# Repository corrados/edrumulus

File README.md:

# Edrumulus

**Edrumulus** is a high quality Open Source e-drum trigger module software which runs on a micro processor.

Project requirements:
- The trigger performance shall be similar to the Roland TD-27.
- Overall latency should be as small as possible. The goal is to achieve a latency < 10 ms.
- The required analog front end design shall be as simple as possible using the fewest number of
  parts possible.

## Videos

## News

Find all important updates of the Edrumulus project in the [change log file](doc/ChangeLog.md)
and in the [discussion forums](https://github.com/corrados/edrumulus/discussions). A road map
of the Edrumulus project can be found in the [TODO file](doc/TODO.md).

## Features

- Positional sensing
- Retrigger cancellation
- Rim shot/cymbol choke detection
- Cross talk cancellation
- Clipping compensation
- Supported micro processor developer boards:
  - **ESP32 (dual core) DEVKIT V1 or similar**
  - **ESP32-S3**
  - **Teensy 4.0/4.1**

## Documentation

- [Manual](doc/manual.md)
- [Algorithm](doc/algorithm.md)

## Prototype hardware

We want to capture the entire signal without non-linear analog preprocessing.
Since micro controllers usually only convert analog signals in the range of 0 to 3.3 V,
we have to move the point of operation in the middle of the voltage range.

A circuit diagram of a simplified prototype which only supports a mono piezo pad and
a hi-hat controller input is given in the following picture:
<br/><br/>

The full circuit diagram of Prototype2 is given in [this PDF file](hardware/prototype2/edrumulus.pdf).

*DISCLAIMER* All these circuit diagrams are used for my first prototypes and work fine for me. Use them
at your own risk. In particular the circuits may not work for currently unsupported pieces of hardware.

## Gallery

A gallery of user implementations of Edrumulus prototypes [can be found here](doc/gallery.md).

## Links

- [EavesDrum](https://eavesdrum.io) ([Source code](https://github.com/tobigun/EavesDrum))

- [eXaDrums](https://exadrums.com) ([Hackaday](https://hackaday.io/project/9350-exadrums), [Source code](https://github.com/SpintroniK/libeXaDrums))

- [Drumidy](https://hackaday.io/project/176712-drumidy-electronic-midi-drum-controller) ([Source code](https://github.com/EvgenyD/Drumidy)): Uses a STM32 processor with 18 inputs and supports re-trigger cancellation.

- [open e-drums](https://open-e-drums.com) ([Source code](https://github.com/RyoKosaka/HelloDrum-arduino-Library))

- [An Arduino based standalone drum kit Hackaday](https://hackaday.io/project/171929-an-arduino-based-standalone-drum-kit) ([Source code](https://hackaday.io/project/171929-an-arduino-based-standalone-drum-kit#menu-files)): Generates audio, too.

- Forum: [How to solve a system of hyperbola equations](https://math.stackexchange.com/questions/3373011/how-to-solve-this-system-of-hyperbola-equations)

- Forum: [E-Drum Technik-Thread (für Elektrotechnik- und Informatik-Interessierte)](https://www.drummerforum.de/forum/71415-e-drum-technik-thread-f%C3%BCr-elektrotechnik-und-informatik-interessierte.html)

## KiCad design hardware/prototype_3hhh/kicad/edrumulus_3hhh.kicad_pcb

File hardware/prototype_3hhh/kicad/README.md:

# edrumulus 3hhh prototype with a Teensy 4.1

PCBA design of the [edrumulus circuit](https://github.com/corrados/edrumulus/blob/661487f7e5eb3b547a28747b91cd4156a5f1f353/hardware/prototype2/edrumulus.pdf) with [modifications by 3hhh](https://github.com/corrados/edrumulus/discussions/98) to be used with a [Teensy 4.1](https://www.pjrc.com/store/teensy41.html) with soldered [pins](https://www.pjrc.com/store/teensy41_pins.html).

## Features

- size: 12x7cm
- price: ~30 EUR plus shipping and tariffs (~10 EUR to EU) at https://jlcpcb.com/ for 5 units (2025)
- little soldering required:
  - female socket for the Teensy 4.1
  - SMD components intended for assembly at the manufacturer
- all 18 Teensy 4.1 analog inputs are connected to respective edrumulus circuits
- female header as "breakout" connector to the drum hardware via DuPont jumper wires: Standard 6,3mm Jack stereo cables can relatively easily be soldered to three male-male jumper wires to connect the board to the drum kit (search "solder wires" on youtube). It may make sense to use short cables for soldering and connect them to longer 6,3mm cables as needed.
- 3hhh modifications:
  - Rp=10k for higher sensitivity
  - some pins (A1-A5) with Rs=100k for low sensitivity needs (kick, ...)
  - some pins (A6-A17) with Rs=10k for high sensitivity needs (snare, hihat, ...)
  - 1N5819WS Schottky diode: cheaper and lower forward voltage than BAT85
- M2 screw holes
- also see [this image](./edrumulus_3hhh.jpg)

## JLCPCB manufacturing

Make sure to select:

- 2 layers
- Suface Finish: LeadFree HASL or ENIG
- Mark on PCB: Order Number(Specify Position)
- PCB Assembly

Manufacturing incl. assembly (PCBA) can be done elsewhere as well, but was optimized for JLCPCB.

## Used software

[KiCad 9](https://www.kicad.org/) with the [JLCPCB plugin](https://github.com/Bouni/kicad-jlcpcb-tools).

Useful presets: https://github.com/sethhillbrand/kicad_templates

Helpful KiCad tutorial: https://www.youtube.com/playlist?list=PLUOaI24LpvQPls1Ru_qECJrENwzD7XImd

## Known issues

- edrumulus currently maxes out at ~15 used analog inputs
- the used female headers tend to run out of stock and may have to be replaced with others
- GND needs to be expanded with a small breadboard

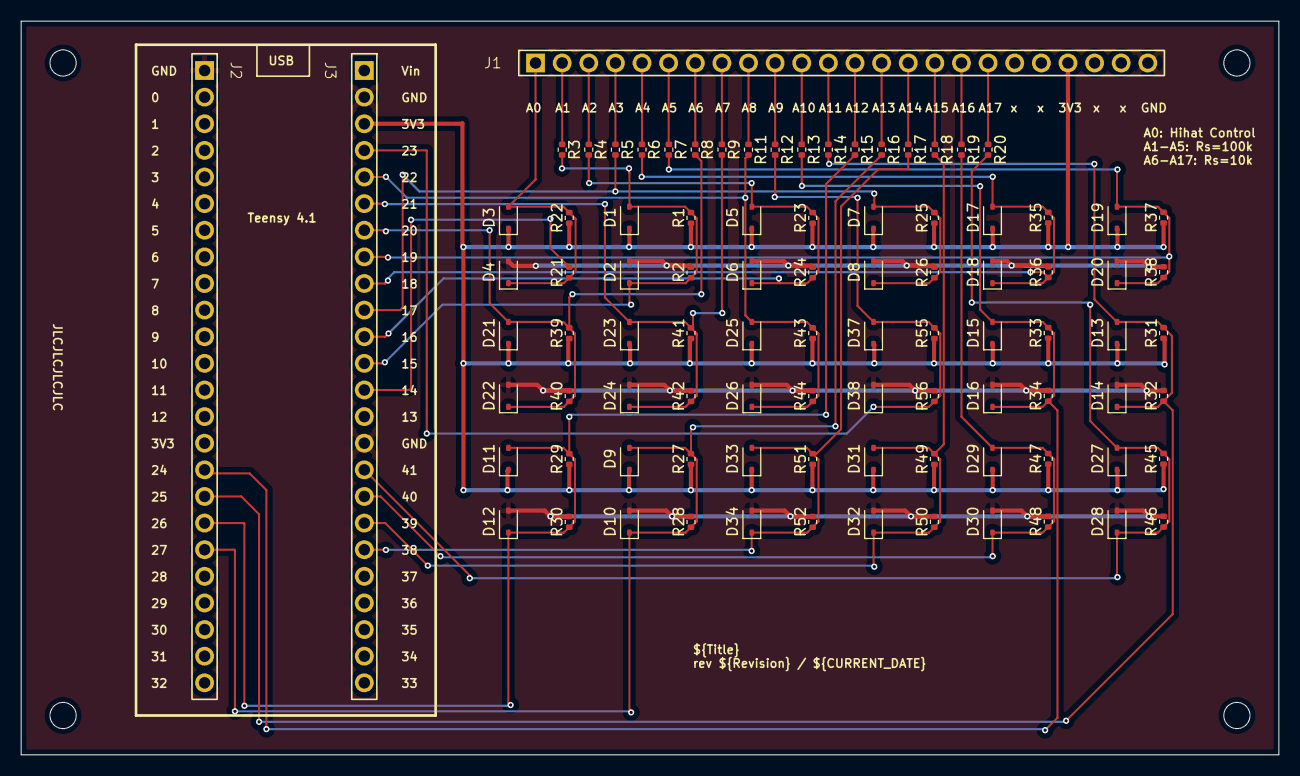
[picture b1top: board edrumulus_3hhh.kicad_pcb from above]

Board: 2 copper layers, 120.0 x 70.0 mm, 92 parts (0 on the bottom side), 38 nets.

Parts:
D1, D2, D3, D4, D5, D6, D7, D8, D9, D10, D11, D12, D13, D14, D15, D16, D17, D18, D19, D20, D21, D22, D23, D24, D25, D26, D27, D28, D29, D30, D31, D32, D33, D34, D37, D38: D; D_SOD-323
J1, J2, J3: Conn_01x24_Socket; 1x24P Female Header Hong Cheng HC-PM254-8.5H-1x24PZ
R1, R2, R8, R9, R11, R12, R13, R14, R15, R16, R17, R18, R19, R20, R21, R22, R23, R24, R25, R26, R27, R28, R29, R30, R31, R32, R33, R34, R35, R36, R37, R38, R39, R40, R41, R42, R43, R44, R45, R46, R47, R48, R49, R50, R51, R52, R55, R56: 10k; R_0402_1005Metric
R3, R4, R5, R6, R7: 100k; R_0402_1005Metric

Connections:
+3V3: D1.1 (K), D3.1 (K), D5.1 (K), D7.1 (K), D9.1 (K), D11.1 (K), D13.1 (K), D15.1 (K), D17.1 (K), D19.1 (K), D21.1 (K), D23.1 (K), D25.1 (K), D27.1 (K), D29.1 (K), D31.1 (K), D33.1 (K), D37.1 (K), J1.21, J3.3, R1.1, R22.1, R23.1, R25.1, R27.1, R29.1, R31.1, R33.1, R35.1, R37.1, R39.1, R41.1, R43.1, R45.1, R47.1, R49.1, R51.1, R55.1
GND: D2.2 (A), D4.2 (A), D6.2 (A), D8.2 (A), D10.2 (A), D12.2 (A), D14.2 (A), D16.2 (A), D18.2 (A), D20.2 (A), D22.2 (A), D24.2 (A), D26.2 (A), D28.2 (A), D30.2 (A), D32.2 (A), D34.2 (A), D38.2 (A), J1.24, J2.1, J3.2, J3.15, R2.2, R24.2, R26.2, R28.2, R30.2, R32.2, R34.2, R36.2, R38.2, R40.2, R42.2, R44.2, R46.2, R48.2, R50.2, R52.2, R56.2
unnamed: D1.2 (A), D2.1 (K), J3.12, R1.2, R2.1, R3.2
unnamed: D3.2 (A), D4.1 (K), J1.1, R21.1, R22.2
unnamed: D5.2 (A), D6.1 (K), J3.11, R4.2, R23.2, R24.1
unnamed: D7.2 (A), D8.1 (K), J3.10, R5.2, R25.2, R26.1
unnamed: D9.2 (A), D10.1 (K), J2.19, R16.2, R27.2, R28.1
unnamed: D11.2 (A), D12.1 (K), J2.18, R15.2, R29.2, R30.1
unnamed: D13.2 (A), D14.1 (K), J2.17, R14.2, R31.2, R32.1
unnamed: D15.2 (A), D16.1 (K), J2.16, R13.2, R33.2, R34.1
unnamed: D17.2 (A), D18.1 (K), J3.9, R6.2, R35.2, R36.1
unnamed: D19.2 (A), D20.1 (K), J3.8, R7.2, R37.2, R38.1
unnamed: D21.2 (A), D22.1 (K), J3.7, R8.2, R39.2, R40.1
unnamed: D23.2 (A), D24.1 (K), J3.6, R9.2, R41.2, R42.1
unnamed: D25.2 (A), D26.1 (K), J3.5, R11.2, R43.2, R44.1
unnamed: D27.2 (A), D28.1 (K), J3.16, R20.2, R45.2, R46.1
unnamed: D29.2 (A), D30.1 (K), J3.17, R19.2, R47.2, R48.1
unnamed: D31.2 (A), D32.1 (K), J3.18, R18.2, R49.2, R50.1
unnamed: D33.2 (A), D34.1 (K), J3.19, R17.2, R51.2, R52.1
unnamed: D37.2 (A), D38.1 (K), J3.4, R12.2, R55.2, R56.1
unnamed: J1.2, R3.1
unnamed: J1.3, R4.1
unnamed: J1.4, R5.1
unnamed: J1.5, R6.1
unnamed: J1.6, R7.1
unnamed: J1.7, R8.1
unnamed: J1.8, R9.1
unnamed: J1.9, R11.1
unnamed: J1.10, R12.1
unnamed: J1.11, R13.1
unnamed: J1.12, R14.1
unnamed: J1.13, R15.1
unnamed: J1.14, R16.1
unnamed: J1.15, R17.1
unnamed: J1.16, R18.1
unnamed: J1.17, R19.1
unnamed: J1.18, R20.1
unnamed: J3.13, R21.2

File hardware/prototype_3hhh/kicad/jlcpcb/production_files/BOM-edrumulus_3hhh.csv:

Comment,Designator,Footprint,LCSC,Quantity
D,"D1,D10,D11,D12,D13,D14,D15,D16,D17,D18,D19,D2,D20,D21,D22,D23,D24,D25,D26,D27,D28,D29,D3,D30,D31,D32,D33,D34,D37,D38,D4,D5,D6,D7,D8,D9",D_SOD-323,C191023,36
100k,"R3,R4,R5,R6,R7",R_0402_1005Metric,C25741,5
10k,"R1,R11,R12,R13,R14,R15,R16,R17,R18,R19,R2,R20,R21,R22,R23,R24,R25,R26,R27,R28,R29,R30,R31,R32,R33,R34,R35,R36,R37,R38,R39,R40,R41,R42,R43,R44,R45,R46,R47,R48,R49,R50,R51,R52,R55,R56,R8,R9",R_0402_1005Metric,C25744,48
Conn_01x24_Socket,"J1,J2,J3",1x24P Female Header Hong Cheng HC-PM254-8.5H-1x24PZ,C41376163,3

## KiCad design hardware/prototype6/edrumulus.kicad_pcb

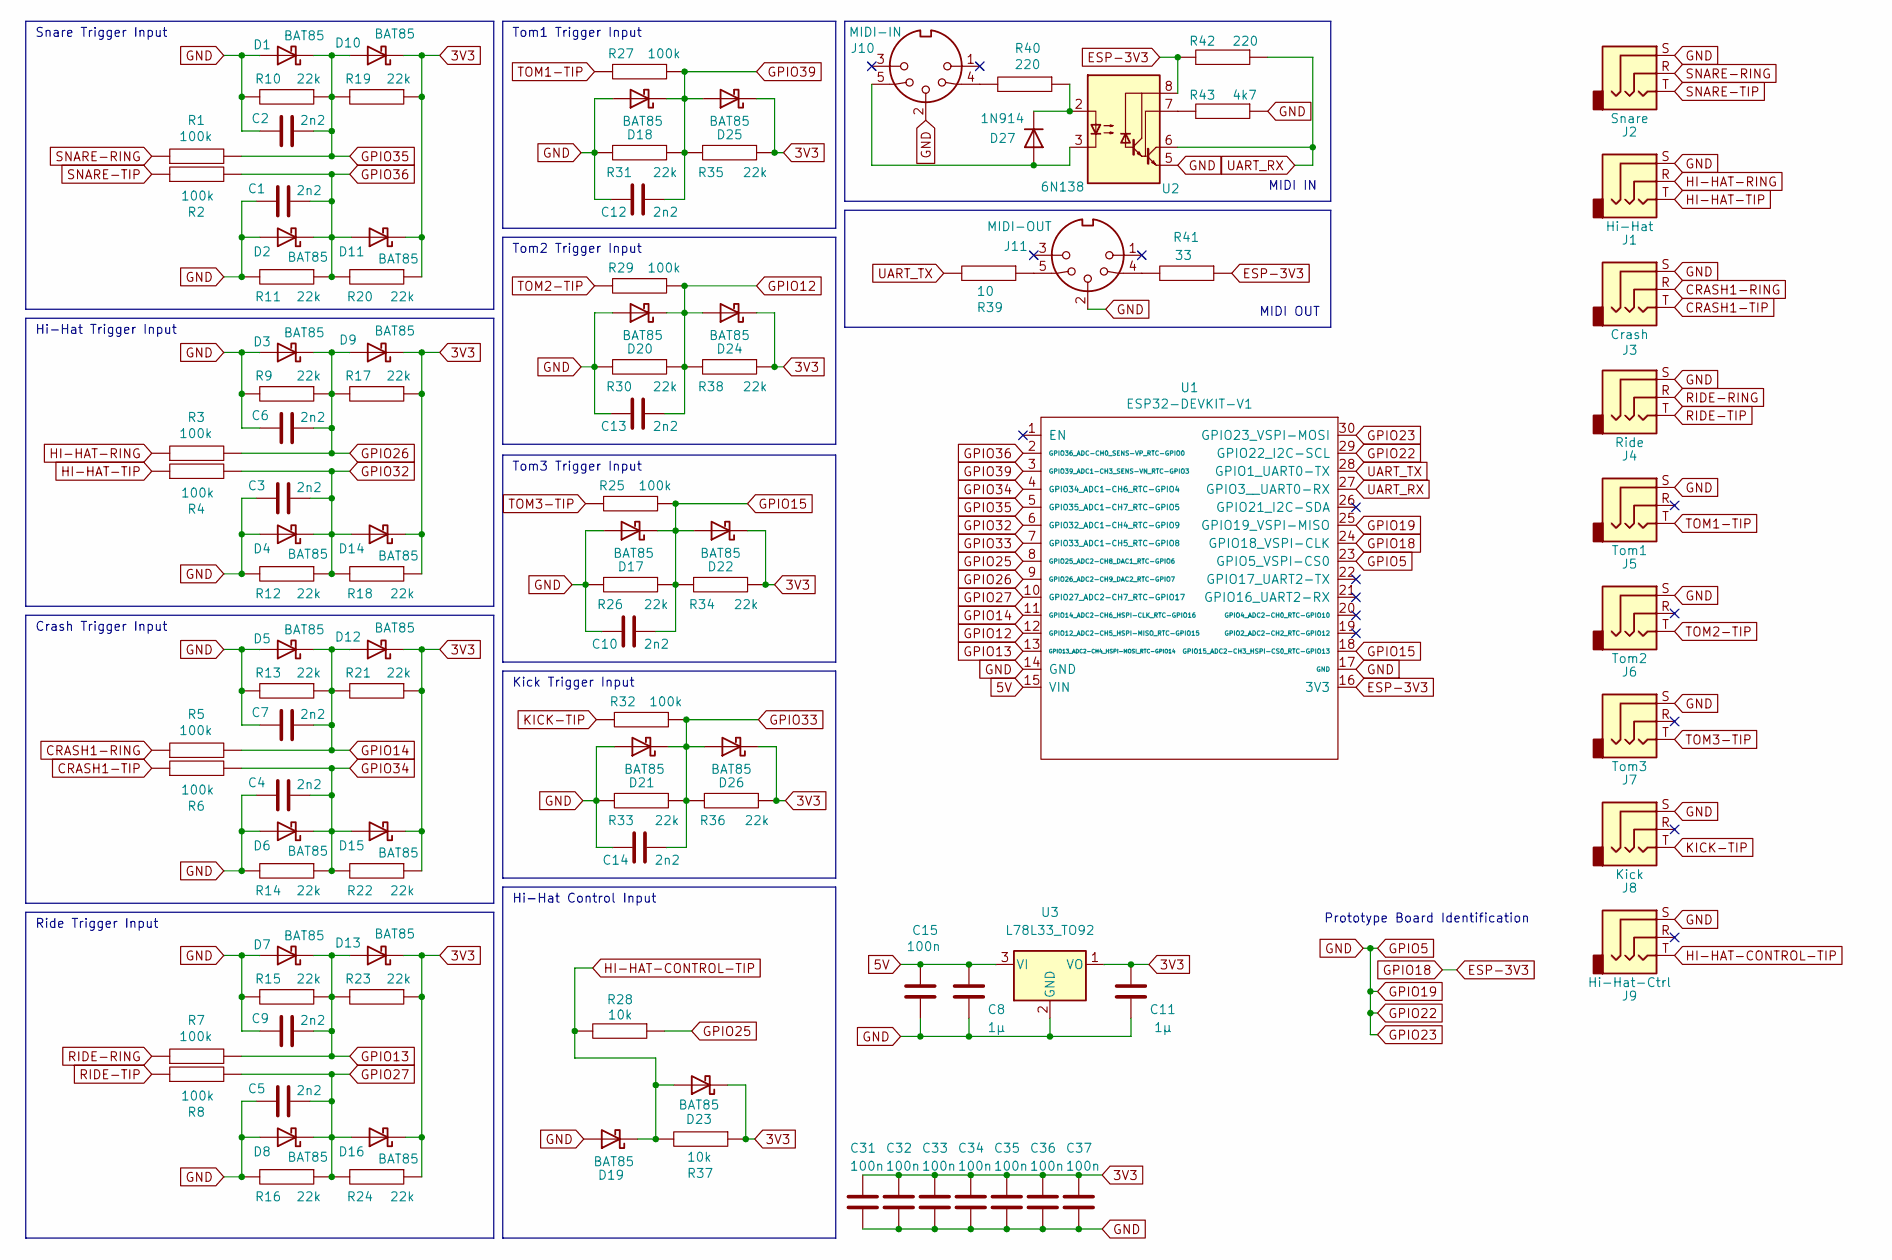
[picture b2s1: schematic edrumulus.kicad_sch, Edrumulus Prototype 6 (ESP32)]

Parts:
C1, C2, C3, C4, C5, C6, C7, C9, C10, C12, C13, C14: 2n2; C_Disc_D5.0mm_W2.5mm_P5.00mm
C8, C11: 1µ; CP_Radial_D8.0mm_P3.50mm
C15, C31, C32, C33, C34, C35, C36, C37: 100n; C_Disc_D5.0mm_W2.5mm_P5.00mm
D1, D2, D3, D4, D5, D6, D7, D8, D9, D10, D11, D12, D13, D14, D15, D16, D17, D18, D19, D20, D21, D22, D23, D24, D25, D26: BAT85; D_DO-35_SOD27_P7.62mm_Horizontal
D27: 1N914; D_DO-35_SOD27_P7.62mm_Horizontal
J1: Hi-Hat; Jack_6.35mm_Neutrik_NMJ6HCD2_Horizontal
J2: Snare; Jack_6.35mm_Neutrik_NMJ6HCD2_Horizontal
J3: Crash; Jack_6.35mm_Neutrik_NMJ6HCD2_Horizontal
J4: Ride; Jack_6.35mm_Neutrik_NMJ6HCD2_Horizontal
J5: Tom1; Jack_6.35mm_Neutrik_NMJ6HCD2_Horizontal
J6: Tom2; Jack_6.35mm_Neutrik_NMJ6HCD2_Horizontal
J7: Tom3; Jack_6.35mm_Neutrik_NMJ6HCD2_Horizontal
J8: Kick; Jack_6.35mm_Neutrik_NMJ6HCD2_Horizontal
J9: Hi-Hat-Ctrl; Jack_6.35mm_Neutrik_NMJ6HCD2_Horizontal
J10: MIDI-IN; DIN-5
J11: MIDI-OUT; DIN-5
R1, R2, R3, R4, R5, R6, R7, R8, R25, R27, R29, R32: 100k; R_Axial_DIN0207_L6.3mm_D2.5mm_P10.16mm_Horizontal
R9, R10, R11, R12, R13, R14, R15, R16, R17, R18, R19, R20, R21, R22, R23, R24, R26, R30, R31, R33, R34, R35, R36, R38: 22k; R_Axial_DIN0207_L6.3mm_D2.5mm_P10.16mm_Horizontal
R28, R37: 10k; R_Axial_DIN0207_L6.3mm_D2.5mm_P10.16mm_Horizontal
R39: 10; R_Axial_DIN0207_L6.3mm_D2.5mm_P10.16mm_Horizontal
R40, R42: 220; R_Axial_DIN0207_L6.3mm_D2.5mm_P10.16mm_Horizontal
R41: 33; R_Axial_DIN0207_L6.3mm_D2.5mm_P10.16mm_Horizontal
R43: 4k7; R_Axial_DIN0207_L6.3mm_D2.5mm_P10.16mm_Horizontal
U1: ESP32-DEVKIT-V1; esp32_devkit_v1
U2: 6N138; DIP-8_W7.62mm_Socket
U3: L78L33_TO92; TO-92_Inline

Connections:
3V3: C11.1, C31.1, C32.1, C33.1, C34.1, C35.1, C36.1, C37.1, D9.1 (K), D10.1 (K), D11.1 (K), D12.1 (K), D13.1 (K), D14.1 (K), D15.1 (K), D16.1 (K), D22.1 (K), D23.1 (K), D24.1 (K), D25.1 (K), D26.1 (K), R17.1, R18.1, R19.1, R20.1, R21.1, R22.1, R23.1, R24.1, R34.1, R35.1, R36.1, R37.1, R38.1, U3.1 (VO)
5V: C8.1, C15.1, U1.15 (VIN), U3.3 (VI)
CRASH1-RING: J3.R, R5.1
CRASH1-TIP: J3.T, R6.1
GPIO5: C1.2, C2.2, C3.2, C4.2, C5.2, C6.2, C7.2, C8.2, C9.2, C10.2, C11.2, C12.2, C13.2, C14.2, C15.2, C31.2, C32.2, C33.2, C34.2, C35.2, C36.2, C37.2, D1.2 (A), D2.2 (A), D3.2 (A), D4.2 (A), D5.2 (A), D6.2 (A), D7.2 (A), D8.2 (A), D17.2 (A), D18.2 (A), D19.2 (A), D20.2 (A), D21.2 (A), J1.S, J2.S, J3.S, J4.S, J5.S, J6.S, J7.S, J8.S, J9.S, J10.2, J11.2, R9.2, R10.2, R11.2, R12.2, R13.2, R14.2, R15.2, R16.2, R26.2, R30.2, R31.2, R33.2, R43.1, U1.14 (GND), U1.17 (GND), U1.23 (GPIO5_VSPI-CS0), U1.25 (GPIO19_VSPI-MISO), U1.29 (GPIO22_I2C-SCL), U1.30 (GPIO23_VSPI-MOSI), U2.5 (GND), U3.2 (GND)
GPIO12: C13.1, D20.1 (K), D24.2 (A), R29.1, R30.1, R38.2, U1.12 (GPIO12_ADC2-CH5_HSPI-MISO_RTC-GPIO15)
GPIO13: C9.1, D7.1 (K), D13.2 (A), R7.2, R15.1, R23.2, U1.13 (GPIO13_ADC2-CH4_HSPI-MOSI_RTC-GPIO14)
GPIO14: C7.1, D5.1 (K), D12.2 (A), R5.2, R13.1, R21.2, U1.11 (GPIO14_ADC2-CH6_HSPI-CLK_RTC-GPIO16)
GPIO15: C10.1, D17.1 (K), D22.2 (A), R25.1, R26.1, R34.2, U1.18 (GPIO15_ADC2-CH3_HSPI-CS0_RTC-GPIO13)
GPIO18: R41.1, R42.2, U1.16 (3V3), U1.24 (GPIO18_VSPI-CLK), U2.8 (VCC)
GPIO25: R28.1, U1.8 (GPIO25_ADC2-CH8_DAC1_RTC-GPIO6)
GPIO26: C6.1, D3.1 (K), D9.2 (A), R3.2, R9.1, R17.2, U1.9 (GPIO26_ADC2-CH9_DAC2_RTC-GPIO7)
GPIO27: C5.1, D8.1 (K), D16.2 (A), R8.2, R16.1, R24.2, U1.10 (GPIO27_ADC2-CH7_RTC-GPIO17)
GPIO32: C3.1, D4.1 (K), D14.2 (A), R4.2, R12.1, R18.2, U1.6 (GPIO32_ADC1-CH4_RTC-GPIO9)
GPIO33: C14.1, D21.1 (K), D26.2 (A), R32.1, R33.1, R36.2, U1.7 (GPIO33_ADC1-CH5_RTC-GPIO8)
GPIO34: C4.1, D6.1 (K), D15.2 (A), R6.2, R14.1, R22.2, U1.4 (GPIO34_ADC1-CH6_RTC-GPIO4)
GPIO35: C2.1, D1.1 (K), D10.2 (A), R1.2, R10.1, R19.2, U1.5 (GPIO35_ADC1-CH7_RTC-GPIO5)
GPIO36: C1.1, D2.1 (K), D11.2 (A), R2.2, R11.1, R20.2, U1.2 (GPIO36_ADC-CH0_SENS-VP_RTC-GPIO0)
GPIO39: C12.1, D18.1 (K), D25.2 (A), R27.1, R31.1, R35.2, U1.3 (GPIO39_ADC1-CH3_SENS-VN_RTC-GPIO3)
HI-HAT-CONTROL-TIP: D19.1 (K), D23.2 (A), J9.T, R28.2, R37.2
HI-HAT-RING: J1.R, R3.1
HI-HAT-TIP: J1.T, R4.1
KICK-TIP: J8.T, R32.2
unnamed: D27.1 (K), R40.1, U2.2 (C1)
unnamed: D27.2 (A), J10.5, U2.3 (C2)
unnamed: J10.4, R40.2
unnamed: J11.4, R41.2
unnamed: J11.5, R39.1
unnamed: R43.2, U2.7 (VO1)
RIDE-RING: J4.R, R7.1
RIDE-TIP: J4.T, R8.1
SNARE-RING: J2.R, R1.1
SNARE-TIP: J2.T, R2.1
TOM1-TIP: J5.T, R27.2
TOM2-TIP: J6.T, R29.2
TOM3-TIP: J7.T, R25.2
UART_RX: R42.1, U1.27 (GPIO3__UART0-RX), U2.6 (VO2)
UART_TX: R39.2, U1.28 (GPIO1_UART0-TX)

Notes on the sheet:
Tom3 Trigger Input
MIDI OUT
Hi-Hat Control Input
Tom1 Trigger Input
Prototype Board Identification
Kick Trigger Input
Ride Trigger Input
Hi-Hat Trigger Input
Snare Trigger Input
Crash Trigger Input
Tom2 Trigger Input
MIDI IN

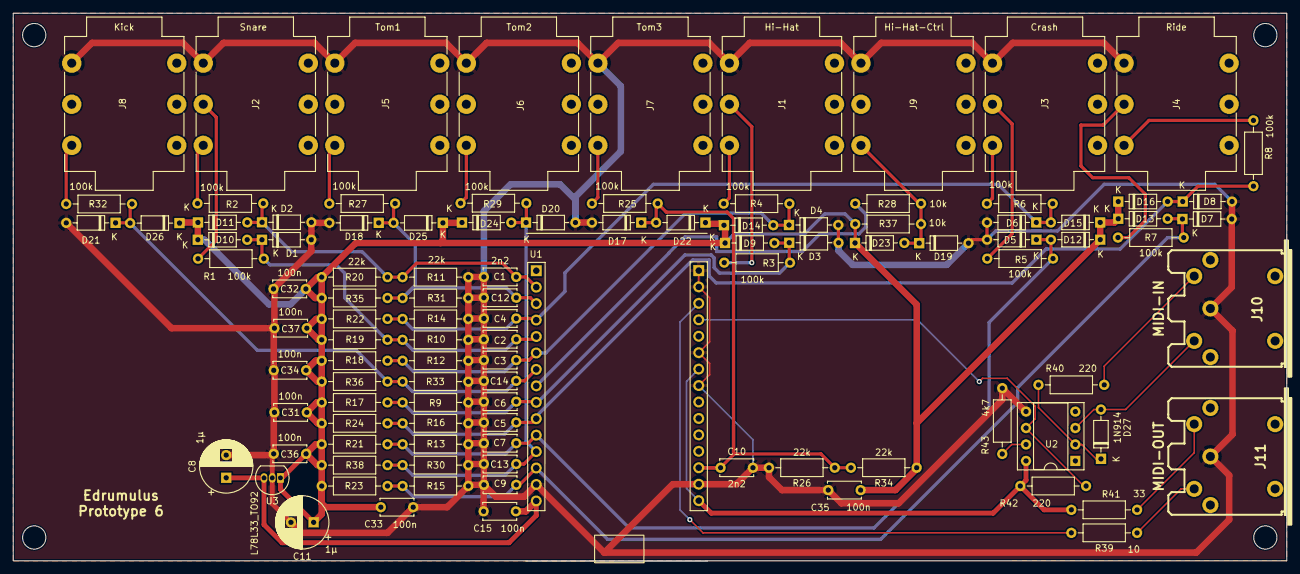
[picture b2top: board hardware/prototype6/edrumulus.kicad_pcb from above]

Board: 2 copper layers, 196.7 x 84.6 mm, 106 parts (0 on the bottom side), 38 nets.

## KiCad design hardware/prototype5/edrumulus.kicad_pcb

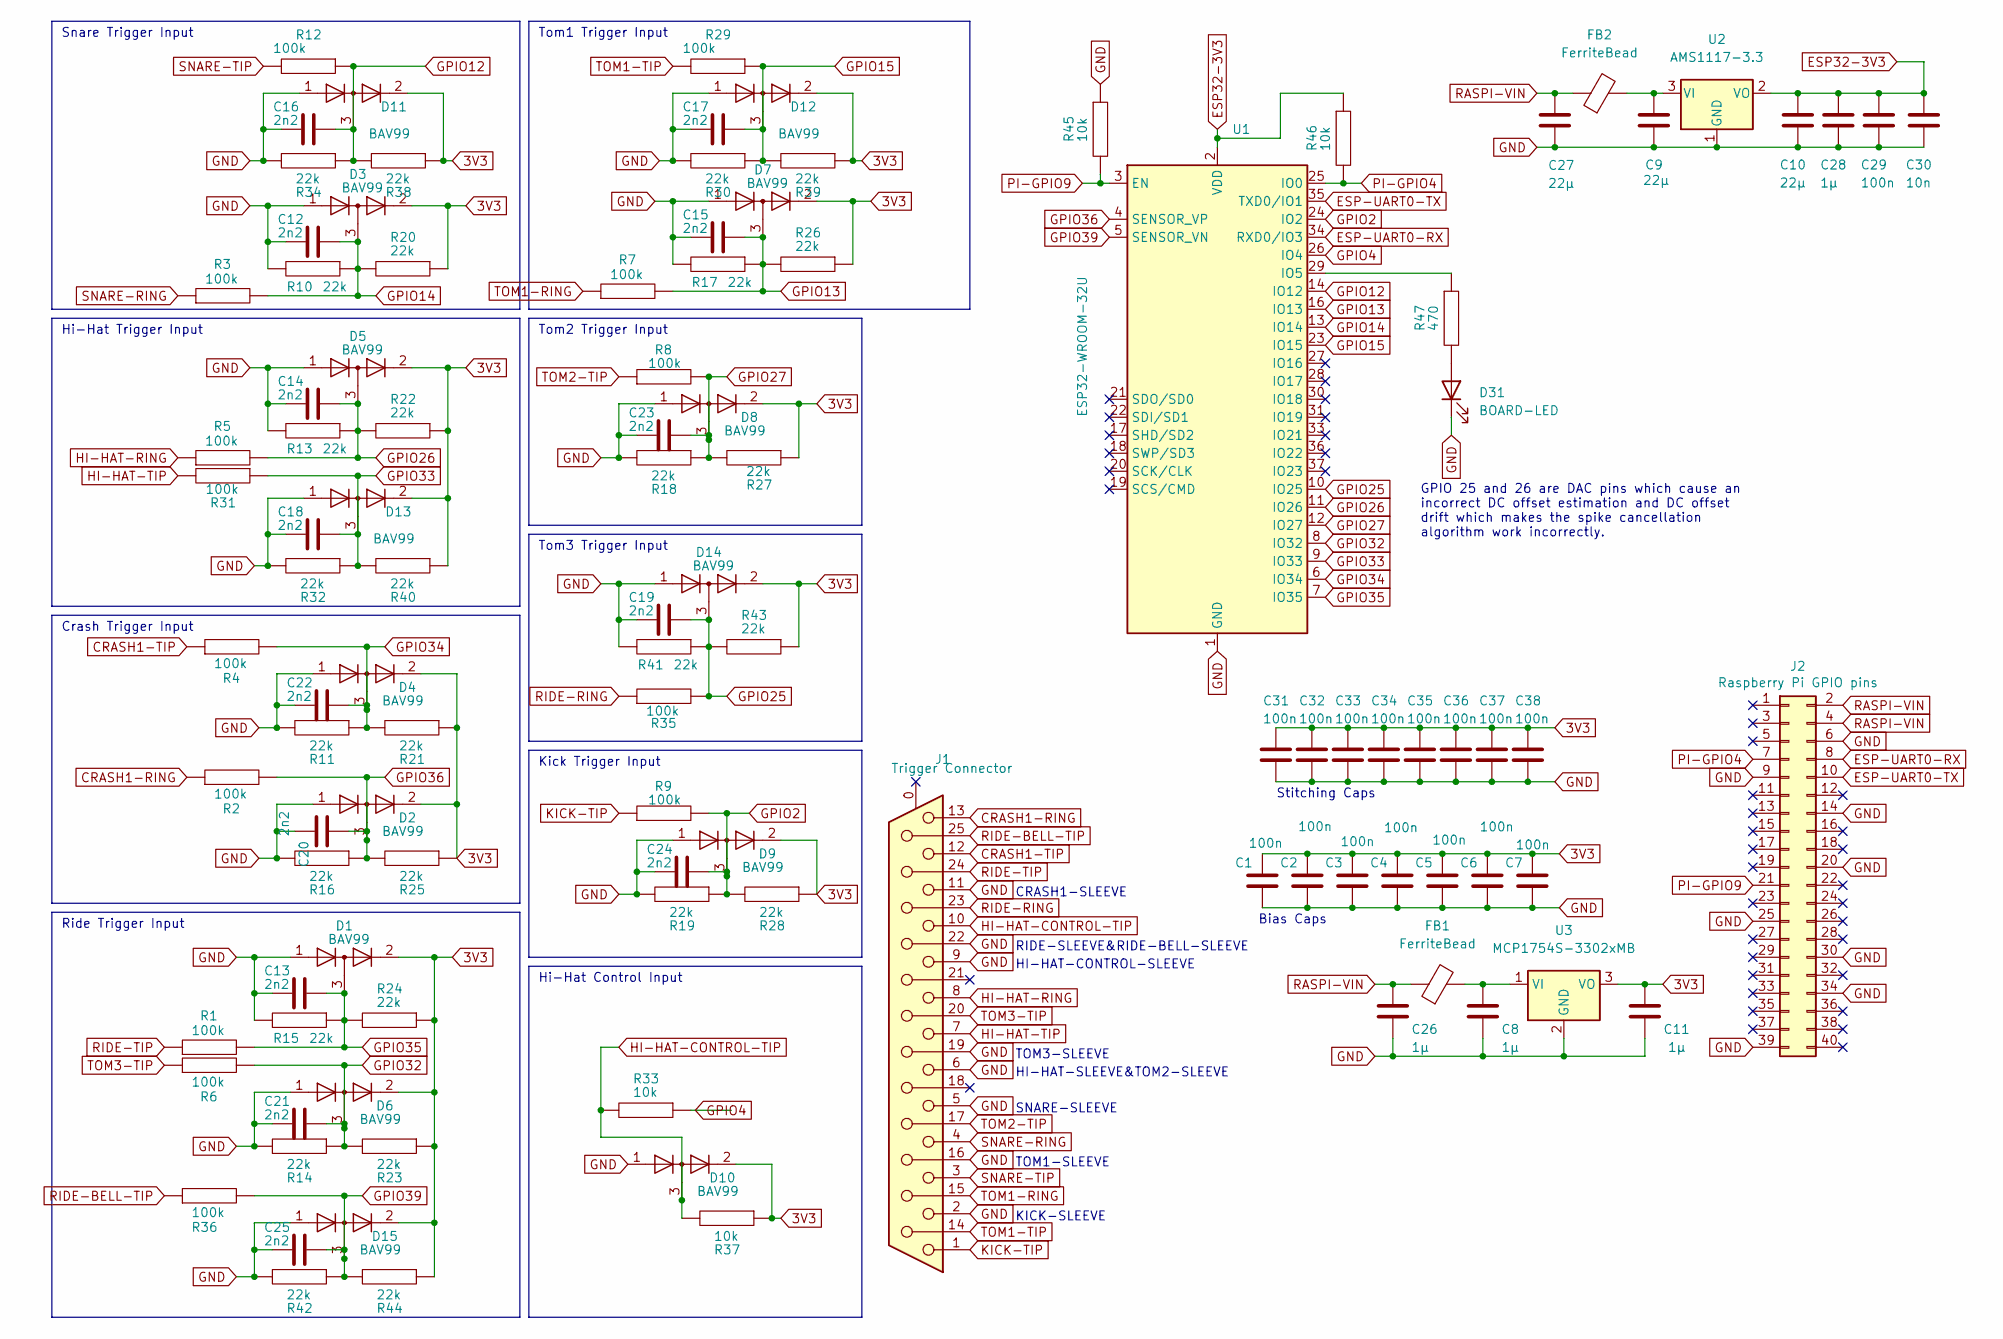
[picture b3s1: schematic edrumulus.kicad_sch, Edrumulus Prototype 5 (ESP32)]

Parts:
C1, C2, C3, C4, C5, C6, C7, C29, C31, C32, C33, C34, C35, C36, C37, C38: 100n; C_0603_1608Metric_Pad1.08x0.95mm_HandSolder
C8, C11, C26, C28: 1µ; C_0603_1608Metric_Pad1.08x0.95mm_HandSolder
C9, C10: 22µ; C_1210_3225Metric_Pad1.33x2.70mm_HandSolder
C12, C13, C14, C15, C16, C17, C18, C19, C20, C21, C22, C23, C24, C25: 2n2; C_0603_1608Metric_Pad1.08x0.95mm_HandSolder
C27: 22µ; C_0603_1608Metric_Pad1.08x0.95mm_HandSolder
C30: 10n; C_0603_1608Metric_Pad1.08x0.95mm_HandSolder
D1, D2, D3, D4, D5, D6, D7, D8, D9, D10, D11, D12, D13, D14, D15: BAV99; SOT-23
D31: BOARD-LED; LED_0603_1608Metric
FB1, FB2: FerriteBead; L_1210_3225Metric_Pad1.42x2.65mm_HandSolder
J1: Trigger Connector; DSUB-25_Female_Horizontal_P2.77x2.84mm_EdgePinOffset7.70mm_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
J2: Raspberry Pi GPIO pins; PinSocket_2x20_P2.54mm_Vertical
R1, R2, R3, R4, R5, R6, R7, R8, R9, R12, R29, R31, R35, R36: 100k; R_0603_1608Metric_Pad0.98x0.95mm_HandSolder
R10, R11, R13, R14, R15, R16, R17, R18, R19, R20, R21, R22, R23, R24, R25, R26, R27, R28, R30, R32, R34, R38, R39, R40, R41, R42, R43, R44: 22k; R_0603_1608Metric_Pad0.98x0.95mm_HandSolder
R33, R37, R45, R46: 10k; R_0603_1608Metric_Pad0.98x0.95mm_HandSolder
R47: 470; R_0603_1608Metric_Pad0.98x0.95mm_HandSolder
U1: ESP32-WROOM-32U
U2: AMS1117-3.3; SOT-223-3_TabPin2
U3: MCP1754S-3302xMB; SOT-89-3

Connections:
3V3: C1.2, C2.2, C3.2, C4.2, C5.2, C6.2, C7.2, C11.1, C31.1, C32.1, C33.1, C34.1, C35.1, C36.1, C37.1, C38.1, D1.2 (A), D2.2 (A), D3.2 (A), D4.2 (A), D5.2 (A), D6.2 (A), D7.2 (A), D8.2 (A), D9.2 (A), D10.2 (A), D11.2 (A), D12.2 (A), D13.2 (A), D14.2 (A), D15.2 (A), R20.1, R21.1, R22.1, R23.1, R24.1, R25.1, R26.1, R27.1, R28.1, R37.1, R38.1, R39.1, R40.1, R43.1, R44.1, U3.3 (VO)
CRASH1-RING: J1.13, R2.1
CRASH1-TIP: J1.12, R4.1
ESP32-3V3: C10.1, C28.1, C29.1, C30.1, R46.1, U1.2 (VDD), U2.2 (VO)
ESP-UART0-RX: J2.8, U1.34 (RXD0/IO3)
ESP-UART0-TX: J2.10, U1.35 (TXD0/IO1)
GPIO2: C24.1, D9.3 (K), R9.2, R19.1, R28.2, U1.24 (IO2)
GPIO4: R33.1, U1.26 (IO4)
GPIO12: C16.1, D11.3 (K), R12.1, R34.1, R38.2, U1.14 (IO12)
GPIO13: C15.1, D7.3 (K), R7.2, R17.1, R26.2, U1.16 (IO13)
GPIO14: C12.1, D3.3 (K), R3.2, R10.1, R20.2, U1.13 (IO14)
GPIO15: C17.1, D12.3 (K), R29.1, R30.1, R39.2, U1.23 (IO15)
GPIO25: C19.1, D14.3 (K), R35.2, R41.1, R43.2, U1.10 (IO25)
GPIO26: C14.1, D5.3 (K), R5.2, R13.1, R22.2, U1.11 (IO26)
GPIO27: C23.1, D8.3 (K), R8.2, R18.1, R27.2, U1.12 (IO27)
GPIO32: C21.1, D6.3 (K), R6.2, R14.1, R23.2, U1.8 (IO32)
GPIO33: C18.1, D13.3 (K), R31.1, R32.1, R40.2, U1.9 (IO33)
GPIO34: C22.1, D4.3 (K), R4.2, R11.1, R21.2, U1.6 (IO34)
GPIO35: C13.1, D1.3 (K), R1.2, R15.1, R24.2, U1.7 (IO35)
GPIO36: C20.1, D2.3 (K), R2.2, R16.1, R25.2, U1.4 (SENSOR_VP)
GPIO39: C25.1, D15.3 (K), R36.2, R42.1, R44.2, U1.5 (SENSOR_VN)
HI-HAT-CONTROL-TIP: D10.3 (K), J1.10, R33.2, R37.2
HI-HAT-RING: J1.8, R5.1
HI-HAT-TIP: J1.7, R31.2
KICK-TIP: J1.1, R9.1
unnamed: C8.1, FB1.2, U3.1 (VI)
unnamed: C9.1, FB2.2, U2.3 (VI)
unnamed: D31.2 (A), R47.2
PI-GPIO4: J2.7, R46.2, U1.25 (IO0)
PI-GPIO9: J2.21, R45.2, U1.3 (EN)
RASPI-VIN: C26.1, C27.1, FB1.1, FB2.1, J2.2, J2.4
RIDE-BELL-TIP: J1.25, R36.1
RIDE-RING: J1.23, R35.1
RIDE-TIP: J1.24, R1.1
SNARE-RING: J1.4, R3.1
SNARE-TIP: J1.3, R12.2
TOM1-RING: J1.15, R7.1
TOM1-TIP: J1.14, R29.2
TOM2-TIP: J1.17, R8.1
TOM3-TIP: J1.20, R6.1

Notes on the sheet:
Snare Trigger Input
KICK-SLEEVE
CRASH1-SLEEVE
SNARE-SLEEVE
HI-HAT-CONTROL-SLEEVE
HI-HAT-SLEEVE&TOM2-SLEEVE
Tom3 Trigger Input
RIDE-SLEEVE&RIDE-BELL-SLEEVE
Tom1 Trigger Input
Bias Caps
GPIO 25 and 26 are DAC pins which cause an incorrect DC offset estimation and DC offset drift which makes the spike cancellation algorithm work incorrectly.
Kick Trigger Input
Crash Trigger Input
Hi-Hat Trigger Input
Hi-Hat Control Input
TOM3-SLEEVE
Stitching Caps
TOM1-SLEEVE
Tom2 Trigger Input
Ride Trigger Input

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
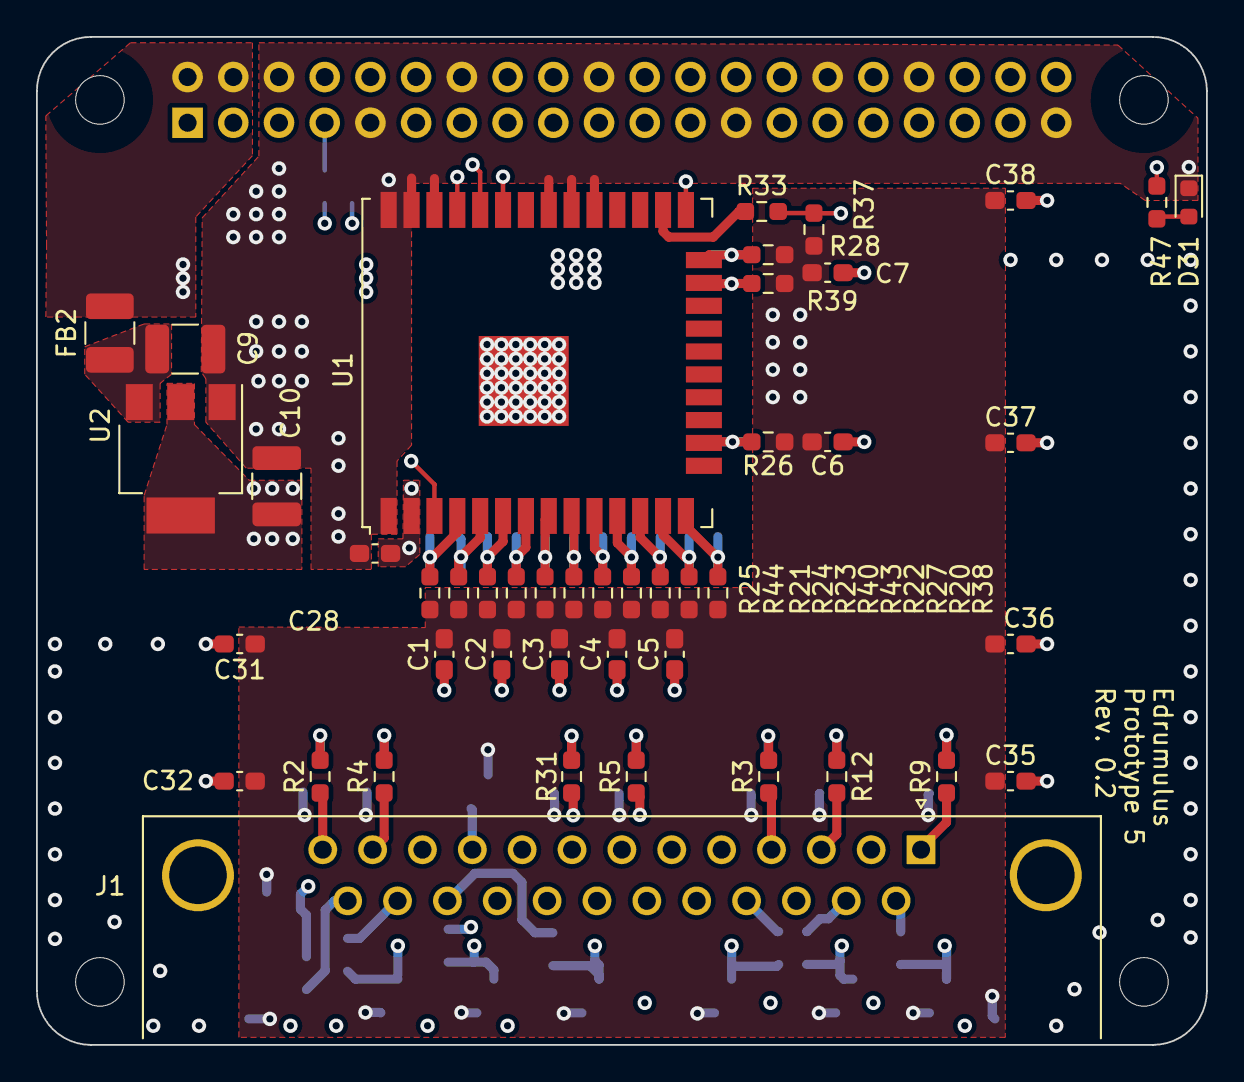
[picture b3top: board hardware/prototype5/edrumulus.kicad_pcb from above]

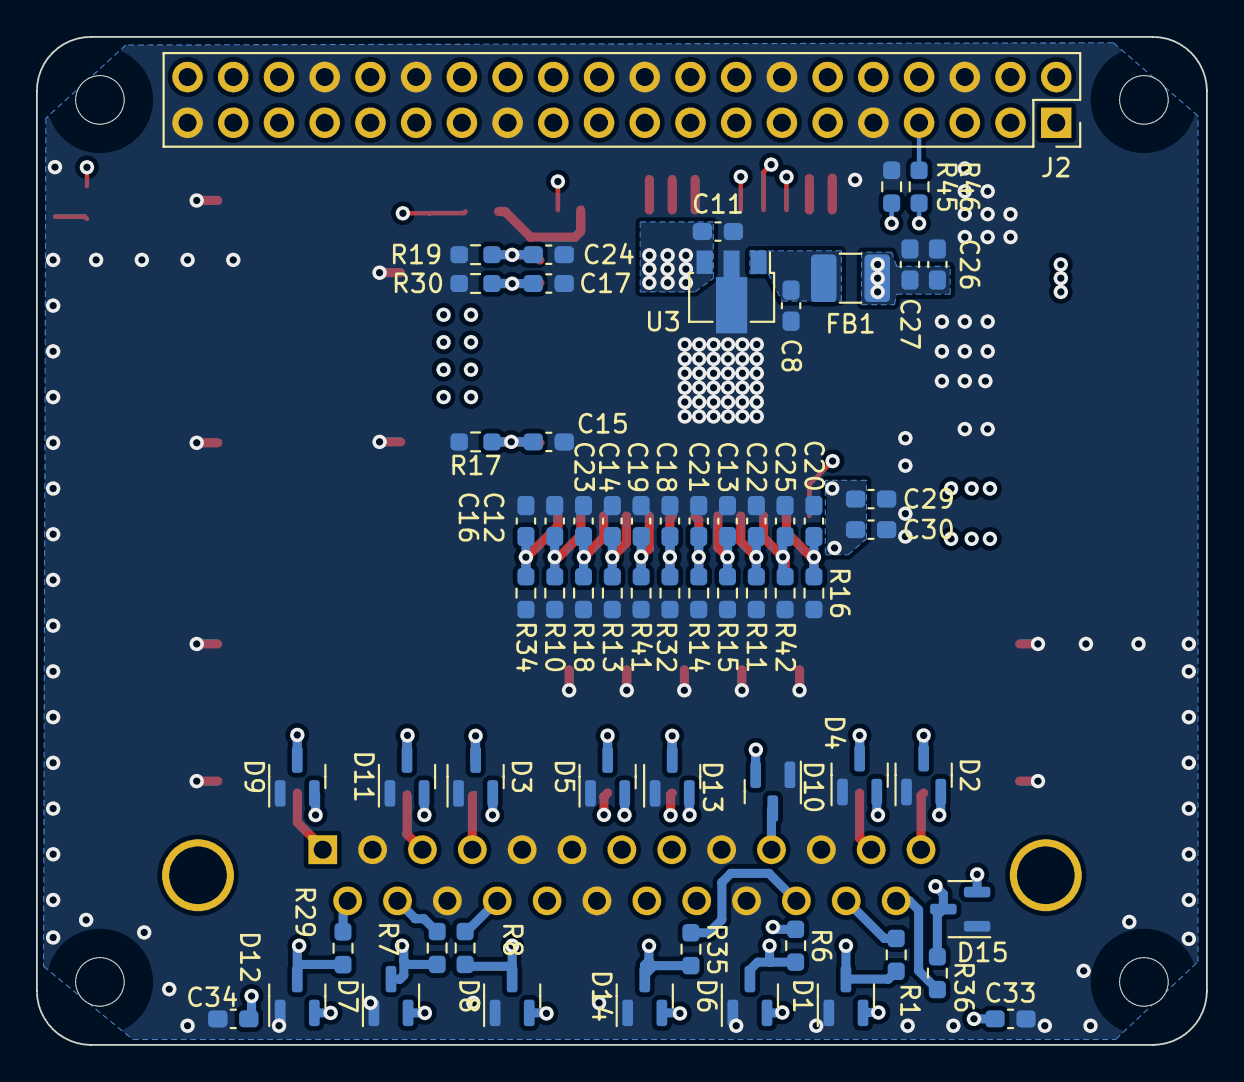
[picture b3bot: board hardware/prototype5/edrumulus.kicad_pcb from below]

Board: 4 copper layers, 65.0 x 56.0 mm, 112 parts (63 on the bottom side), 42 nets.

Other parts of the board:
MH1, MH2, MH3, MH4: MountingHole_2.7mm_M2.5

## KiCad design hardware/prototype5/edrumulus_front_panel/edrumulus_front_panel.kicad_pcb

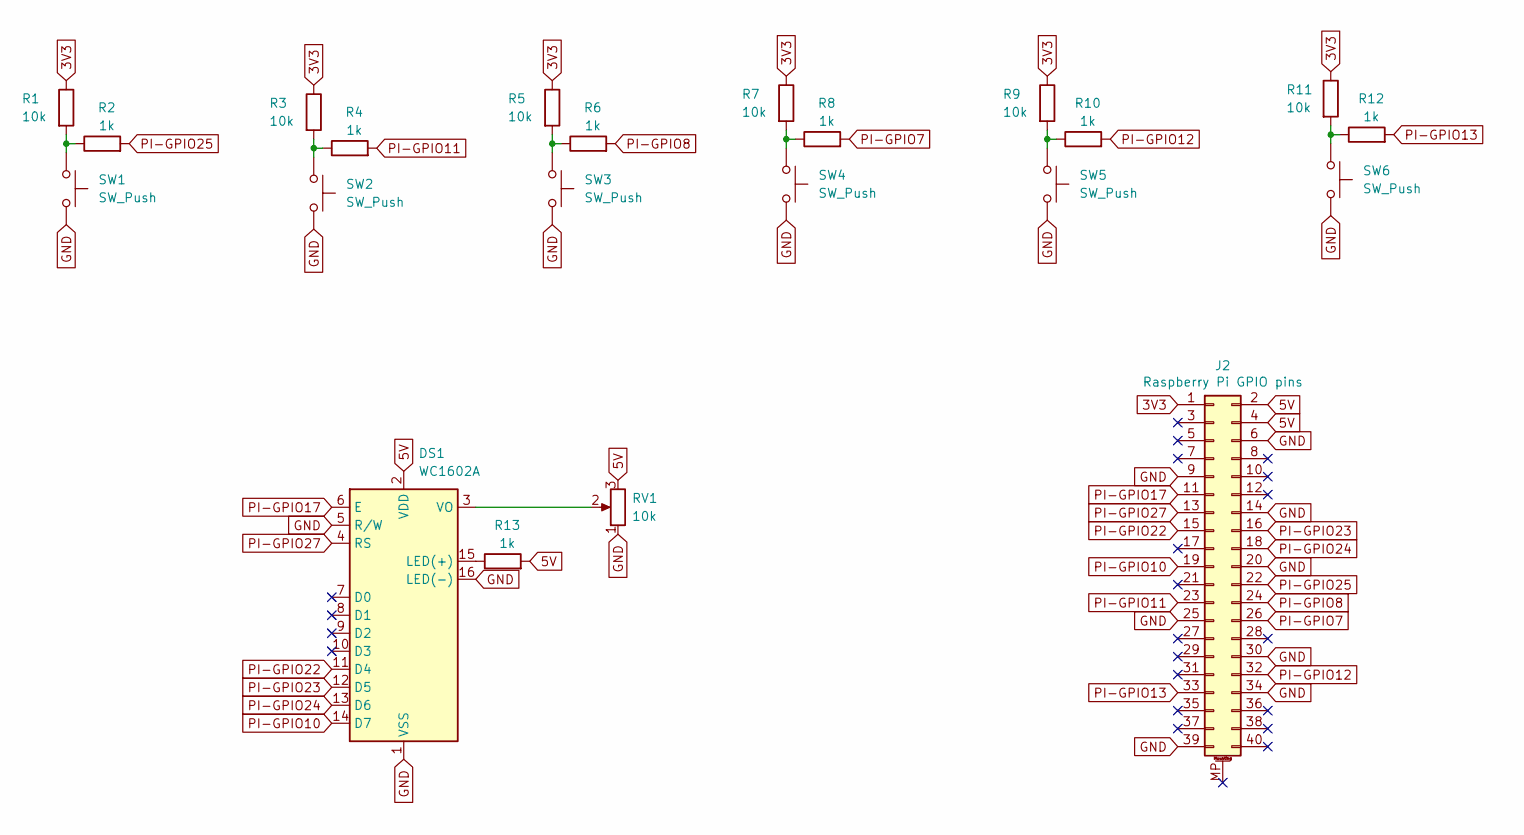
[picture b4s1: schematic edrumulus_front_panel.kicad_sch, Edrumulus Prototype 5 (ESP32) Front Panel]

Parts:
DS1: WC1602A
J2: Raspberry Pi GPIO pins; PinHeader_2x20_P2.54mm_Vertical
R1, R3, R5, R7, R9, R11: 10k; R_1206_3216Metric_Pad1.30x1.75mm_HandSolder
R2, R4, R6, R8, R10, R12, R13: 1k; R_1206_3216Metric_Pad1.30x1.75mm_HandSolder
RV1: 10k; Potentiometer_ACP_CA9-H2,5_Horizontal
SW1, SW2, SW3, SW4, SW5, SW6: SW_Push; SW_PUSH_6mm_H7.3mm

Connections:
3V3: J2.1, R1.1, R3.1, R5.1, R7.1, R9.1, R11.1
5V: DS1.2 (VDD), J2.2, J2.4, R13.2, RV1.3
GND: DS1.1 (VSS), DS1.5 (R/W), DS1.16 (LED(-)), J2.6, J2.9, J2.14, J2.20, J2.25, J2.30, J2.34, J2.39, RV1.1, SW1.2, SW2.2, SW3.2, SW4.2, SW5.2, SW6.2
unnamed: DS1.3 (VO), RV1.2
unnamed: DS1.15 (LED(+)), R13.1
unnamed: R1.2, R2.1, SW1.1
unnamed: R3.2, R4.1, SW2.1
unnamed: R5.2, R6.1, SW3.1
unnamed: R7.2, R8.1, SW4.1
unnamed: R9.2, R10.1, SW5.1
unnamed: R11.2, R12.1, SW6.1
PI-GPIO7: J2.26, R8.2
PI-GPIO8: J2.24, R6.2
PI-GPIO10: DS1.14 (D7), J2.19
PI-GPIO11: J2.23, R4.2
PI-GPIO12: J2.32, R10.2
PI-GPIO13: J2.33, R12.2
PI-GPIO17: DS1.6 (E), J2.11
PI-GPIO22: DS1.11 (D4), J2.15
PI-GPIO23: DS1.12 (D5), J2.16
PI-GPIO24: DS1.13 (D6), J2.18
PI-GPIO25: J2.22, R2.2
PI-GPIO27: DS1.4 (RS), J2.13

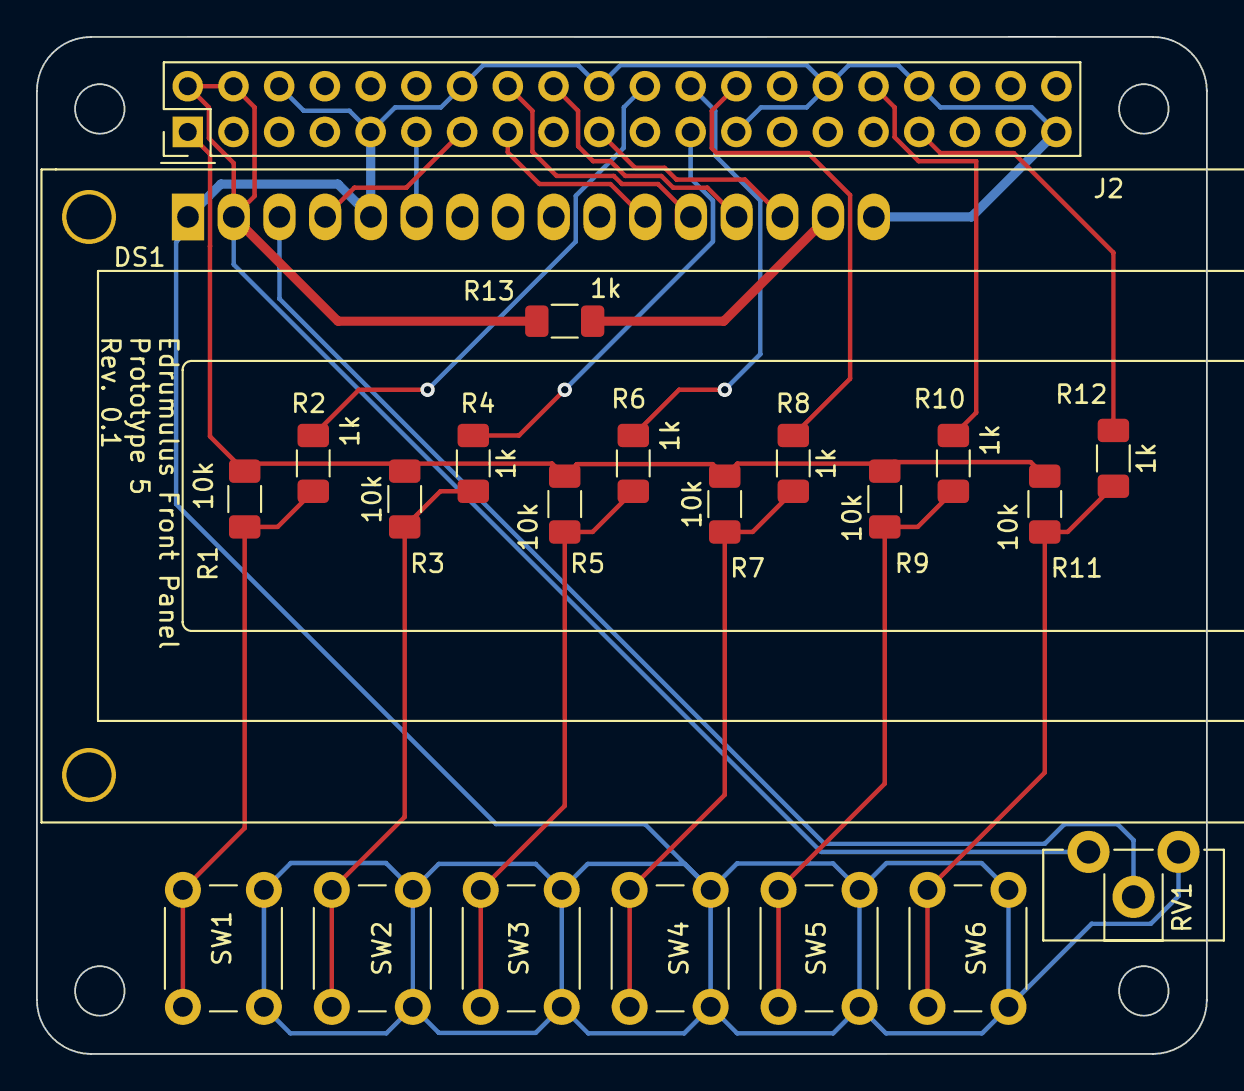
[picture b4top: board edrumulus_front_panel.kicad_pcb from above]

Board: 2 copper layers, 65.0 x 56.5 mm, 22 parts (0 on the bottom side), 23 nets.
